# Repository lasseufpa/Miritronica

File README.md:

# Miritronica 

O Miritrônica (Miriti com Eletrônica) tem como objetivo unir os avanços tecnológicos com a tradição dos brinquedos de miriti.

## Projetos em andamento:

* Barco de miriti controlado pelo celular
* [Robô de miriti Wall-Ti](https://github.com/lasseufpa/Miritronica/wiki/Projeto-Wall-Ti)
* Bonecos Folclóricos

# Como participar:

Adote uma tarefa [aqui](https://github.com/lasseufpa/Miritronica/issues)

ou entre em contato através do [forum](https://www.quicktopic.com/52/H/xq95KSk64Q3vZ).

Temos reuniões semanais (normlmente as sextas pela manhã) com duração de 1h no LASSE-PCT.

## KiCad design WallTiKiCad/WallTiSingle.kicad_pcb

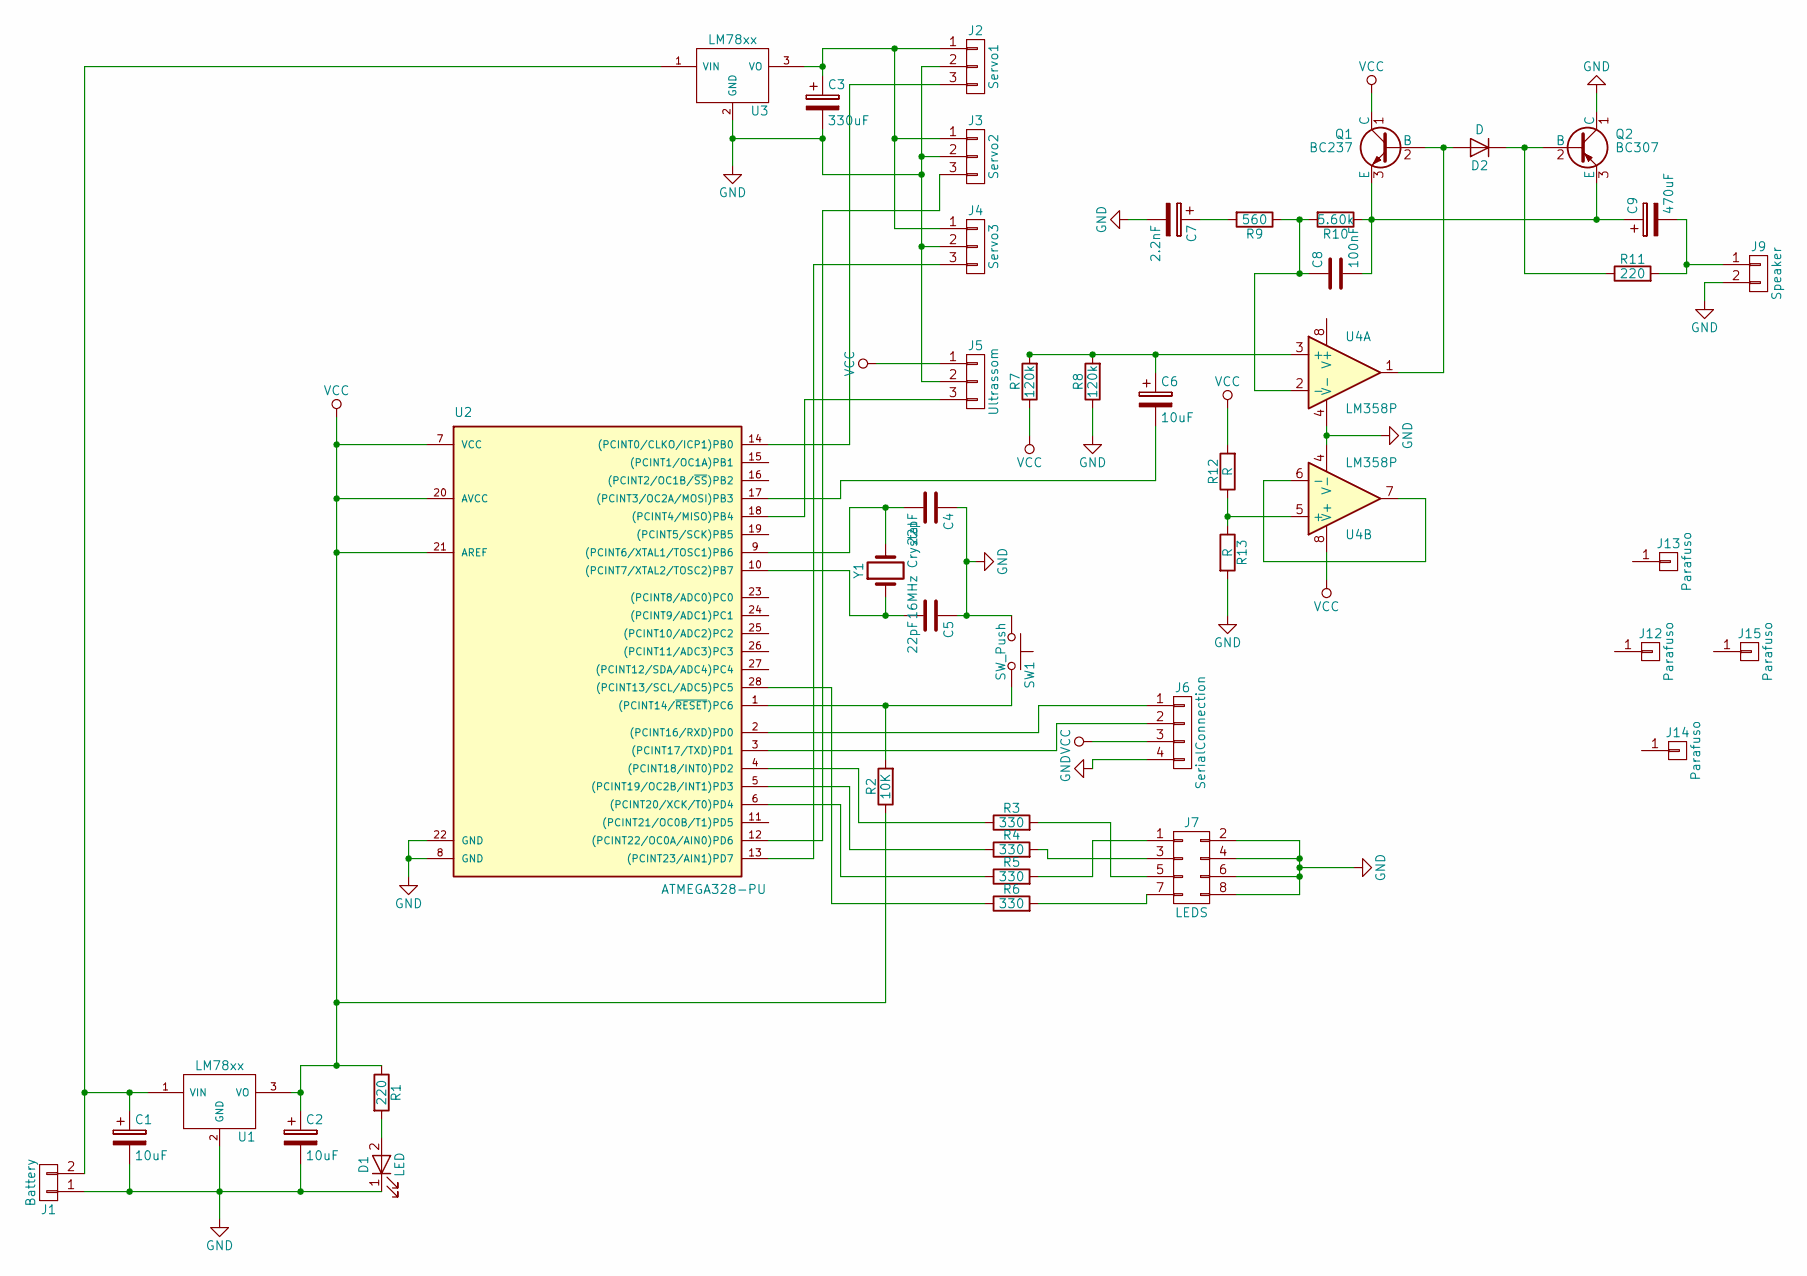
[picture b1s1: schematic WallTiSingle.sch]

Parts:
C1, C2, C6: 10uF; CP_Radial_D6.3mm_P2.50mm
C3: 330uF; CP_Radial_D10.0mm_P5.00mm
C4, C5: 22pF; C_Disc_D5.0mm_W2.5mm_P5.00mm
C7: 2.2nF; CP_Radial_D5.0mm_P2.00mm
C8: 100nF; C_Disc_D11.0mm_W5.0mm_P10.00mm
C9: 470uF; CP_Radial_D10.0mm_P5.00mm
D1: LED; LED_D5.0mm
D2: D; D_DO-41_SOD81_P10.16mm_Horizontal
J1: Battery; PINHEAD1-2
J2: Servo1; PINHEAD1-3
J3: Servo2; PINHEAD1-3
J4: Servo3; PINHEAD1-3
J5: Ultrassom; PINHEAD1-3
J6: SerialConnection; Pin_Header_Straight_1x04_Pitch2.54mm
J7: LEDS; Pin_Header_Straight_2x04_Pitch2.54mm
J9: Speaker; PINHEAD1-2
J12, J13, J14, J15: Parafuso; MountingHole_3.2mm_M3_DIN965_Pad
Q1: BC237; TO-92_Molded_Narrow
Q2: BC307; TO-92_Molded_Narrow
R1, R11: 220; R_Axial_DIN0207_L6.3mm_D2.5mm_P10.16mm_Horizontal
R2: 10K; R_Axial_DIN0207_L6.3mm_D2.5mm_P10.16mm_Horizontal
R3, R4, R5, R6: 330; R_Axial_DIN0207_L6.3mm_D2.5mm_P10.16mm_Horizontal
R7, R8: 120k; R_Axial_DIN0207_L6.3mm_D2.5mm_P10.16mm_Horizontal
R9: 560; R_Axial_DIN0207_L6.3mm_D2.5mm_P10.16mm_Horizontal
R10: 5.60k; R_Axial_DIN0207_L6.3mm_D2.5mm_P10.16mm_Horizontal
R12, R13: R; R_Axial_DIN0207_L6.3mm_D2.5mm_P10.16mm_Horizontal
SW1: SW_Push; SW_PUSH_6mm_h5mm
U1, U3: LM78xx; TO-220_Vertical
U2: ATMEGA328-PU; DIP-28_W7.62mm_Socket_LongPads
U4: LM358P; DIP-8_W7.62mm_Socket_LongPads
Y1: 16MHz Crystal; Resonator-2pin_w10.0mm_h5.0mm

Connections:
GND: C1.2, C2.2, C3.2, C4.1, C5.1, C7.2, D1.1 (K), J1.1, J2.2, J3.2, J4.2, J5.2, J6.4, J7.2, J7.4, J7.6, J7.8, J9.2, Q2.1 (C), R8.1, R13.2, SW1.1, U1.2 (GND), U2.8 (GND), U2.22 (GND), U3.2 (GND), U4.4 (V-)
unnamed: C1.1, J1.2, U1.1 (VIN), U3.1 (VIN)
unnamed: C3.1, J2.1, J3.1, J4.1, U3.3 (VO)
unnamed: C4.2, U2.9 ((PCINT6/XTAL1/TOSC1)PB6), Y1.2
unnamed: C5.2, U2.10 ((PCINT7/XTAL2/TOSC2)PB7), Y1.1
unnamed: C6.1, R7.2, R8.2, U4.3 (+)
unnamed: C6.2, U2.17 ((PCINT3/OC2A/MOSI)PB3)
unnamed: C7.1, R9.2
unnamed: C8.1, R9.1, R10.2, U4.2 (-)
unnamed: C8.2, C9.1, Q1.3 (E), Q2.3 (E), R10.1
unnamed: C9.2, J9.1, R11.2
unnamed: D1.2 (A), R1.2
unnamed: D2.1 (K), Q2.2 (B), R11.1
unnamed: D2.2 (A), Q1.2 (B), U4.1
unnamed: J2.3, U2.14 ((PCINT0/CLKO/ICP1)PB0)
unnamed: J3.3, U2.12 ((PCINT22/OC0A/AIN0)PD6)
unnamed: J4.3, U2.13 ((PCINT23/AIN1)PD7)
unnamed: J5.3, U2.18 ((PCINT4/MISO)PB4)
unnamed: J6.1, U2.2 ((PCINT16/RXD)PD0)
unnamed: J6.2, U2.3 ((PCINT17/TXD)PD1)
unnamed: J7.1, R5.2
unnamed: J7.3, R4.2
unnamed: J7.5, R3.2
unnamed: J7.7, R6.2
unnamed: R2.2, SW1.2, U2.1 ((PCINT14/~RESET~)PC6)
unnamed: R3.1, U2.4 ((PCINT18/INT0)PD2)
unnamed: R4.1, U2.5 ((PCINT19/OC2B/INT1)PD3)
unnamed: R5.1, U2.6 ((PCINT20/XCK/T0)PD4)
unnamed: R6.1, U2.28 ((PCINT13/SCL/ADC5)PC5)
unnamed: R12.1, R13.1, U4.5 (+)
unnamed: U4.6 (-), U4.7
VCC: C2.1, J5.1, J6.3, Q1.1 (C), R1.1, R2.1, R7.1, R12.2, U1.3 (VO), U2.7 (VCC), U2.20 (AVCC), U2.21 (AREF), U4.8 (V+)

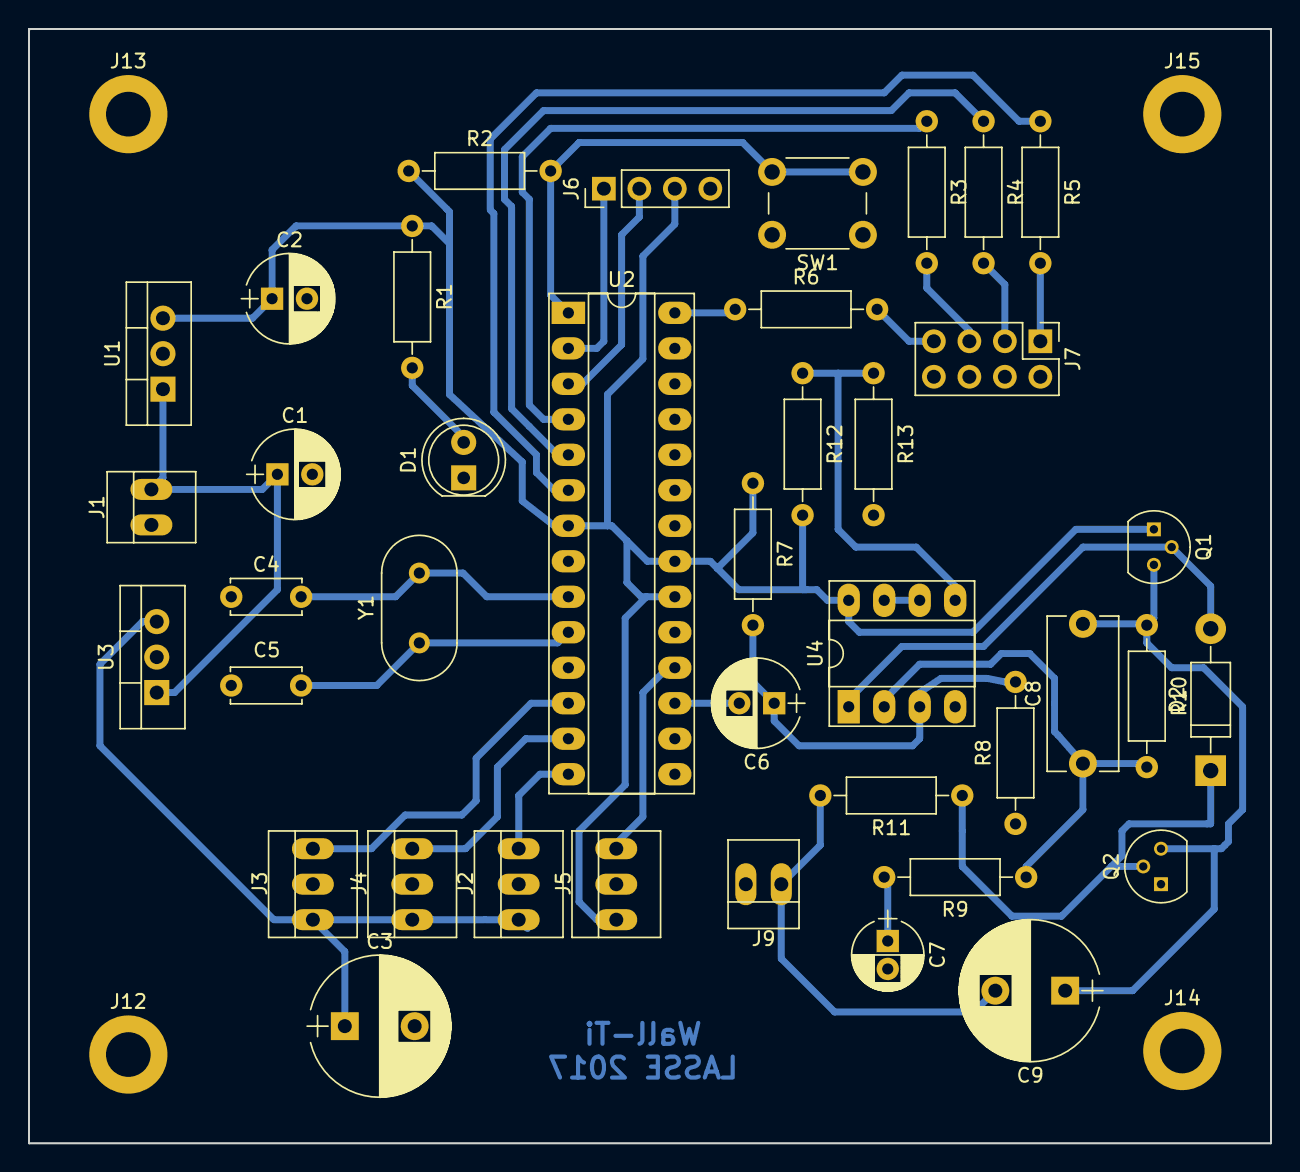
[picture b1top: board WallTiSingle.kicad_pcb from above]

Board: 2 copper layers, 88.9 x 79.8 mm, 44 parts (0 on the bottom side), 32 nets.

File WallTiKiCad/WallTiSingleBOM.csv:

Reference, Value, Footprint, Datasheet
U4,LM358P,Housings_DIP:DIP-8_W7.62mm_Socket_LongPads,
R9,560,Resistors_THT:R_Axial_DIN0207_L6.3mm_D2.5mm_P10.16mm_Horizontal,
R10,5.60k,Resistors_THT:R_Axial_DIN0207_L6.3mm_D2.5mm_P10.16mm_Horizontal,
Q1,BC237,TO_SOT_Packages_THT:TO-92_Molded_Narrow,
D2,D,Diodes_THT:D_DO-41_SOD81_P10.16mm_Horizontal,
Q2,BC307,TO_SOT_Packages_THT:TO-92_Molded_Narrow,
R11,220,Resistors_THT:R_Axial_DIN0207_L6.3mm_D2.5mm_P10.16mm_Horizontal,
C8,100nF,Capacitors_THT:C_Disc_D11.0mm_W5.0mm_P10.00mm,
R7,120k,Resistors_THT:R_Axial_DIN0207_L6.3mm_D2.5mm_P10.16mm_Horizontal,
R8,120k,Resistors_THT:R_Axial_DIN0207_L6.3mm_D2.5mm_P10.16mm_Horizontal,
C5,22pF,Capacitors_THT:C_Disc_D5.0mm_W2.5mm_P5.00mm,
Y1,16MHz Crystal,Crystals:Resonator-2pin_w10.0mm_h5.0mm,
C4,22pF,Capacitors_THT:C_Disc_D5.0mm_W2.5mm_P5.00mm,
D1,LED,LEDs:LED_D5.0mm,
R1,220,Resistors_THT:R_Axial_DIN0207_L6.3mm_D2.5mm_P10.16mm_Horizontal,
U2,ATMEGA328-PU,Housings_DIP:DIP-28_W7.62mm_Socket_LongPads,
R2,10K,Resistors_THT:R_Axial_DIN0207_L6.3mm_D2.5mm_P10.16mm_Horizontal,
J9,Speaker,Connectors:PINHEAD1-2,
J1,Battery,Connectors:PINHEAD1-2,
R5,330,Resistors_THT:R_Axial_DIN0207_L6.3mm_D2.5mm_P10.16mm_Horizontal,
R4,330,Resistors_THT:R_Axial_DIN0207_L6.3mm_D2.5mm_P10.16mm_Horizontal,
R3,330,Resistors_THT:R_Axial_DIN0207_L6.3mm_D2.5mm_P10.16mm_Horizontal,
R6,330,Resistors_THT:R_Axial_DIN0207_L6.3mm_D2.5mm_P10.16mm_Horizontal,
J2,Servo1,Connectors:PINHEAD1-3,
J3,Servo2,Connectors:PINHEAD1-3,
J4,Servo3,Connectors:PINHEAD1-3,
J5,Ultrassom,Connectors:PINHEAD1-3,
C2,10uF,Capacitors_THT:CP_Radial_D6.3mm_P2.50mm,
C1,10uF,Capacitors_THT:CP_Radial_D6.3mm_P2.50mm,
C3,330uF,Capacitors_THT:CP_Radial_D10.0mm_P5.00mm,
C9,470uF,Capacitors_THT:CP_Radial_D10.0mm_P5.00mm,
C7,2.2nF,Capacitors_THT:CP_Radial_D5.0mm_P2.00mm,
C6,10uF,Capacitors_THT:CP_Radial_D6.3mm_P2.50mm,
SW1,SW_Push,Buttons_Switches_THT:SW_PUSH_6mm_h5mm,
U3,LM78xx,TO_SOT_Packages_THT:TO-220_Vertical,
U1,LM78xx,TO_SOT_Packages_THT:TO-220_Vertical,
R12,R,Resistors_THT:R_Axial_DIN0207_L6.3mm_D2.5mm_P10.16mm_Horizontal,
R13,R,Resistors_THT:R_Axial_DIN0207_L6.3mm_D2.5mm_P10.16mm_Horizontal,
J13,Parafuso,Mounting_Holes:MountingHole_3.2mm_M3_DIN965_Pad,
J12,Parafuso,Mounting_Holes:MountingHole_3.2mm_M3_DIN965_Pad,
J14,Parafuso,Mounting_Holes:MountingHole_3.2mm_M3_DIN965_Pad,
J15,Parafuso,Mounting_Holes:MountingHole_3.2mm_M3_DIN965_Pad,
J6,SerialConnection,Pin_Headers:Pin_Header_Straight_1x04_Pitch2.54mm,
J7,LEDS,Pin_Headers:Pin_Header_Straight_2x04_Pitch2.54mm,

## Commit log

2016-11-12 Wall-ti code
2016-11-30 Code em 1 arduino
    Juntei o code dos dois arduinos em um só, removendo a biblioteca do servo que causava conflito, agora os servos se movem através de loops dentro do código que usam frequência/duração do pulso para os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
2016-11-30 Pequenas correções e adição da cabeça no movimento
    Adicionei as rotações que a cabeça do robô deve fazer (45~135 graus)e
    apliquei algumas correções nos code.
2017-01-06 Commit inicial
    Commit contendo os protótipos de códigos que vão rodar no
    microcontrolador do barco e no aplicativo responsável pelo controle.
    Melhorias Pendentes:
    * Visual do App
    * Implementação do código do motor DC
    * Função de retorno automático dos servo para a posição inicial
2017-06-08 Code teste de motor DC
2017-06-12 adicionando codigo para 1 arduino e projeto da placa feito no KiCad
2017-09-13 Atualização up down
    Correção no código para mover "up down" pra compatibilidade com o app
2017-09-21 App com ícone
2017-09-26 Adicionado esquematico do barco
2017-09-26 alteracao no esquematico barco
2017-09-26 Codigo sem realinhamento do leme
2017-09-28 Modificações no app. Busca de dispositivos bluetooth implementada. Info atualizado.
